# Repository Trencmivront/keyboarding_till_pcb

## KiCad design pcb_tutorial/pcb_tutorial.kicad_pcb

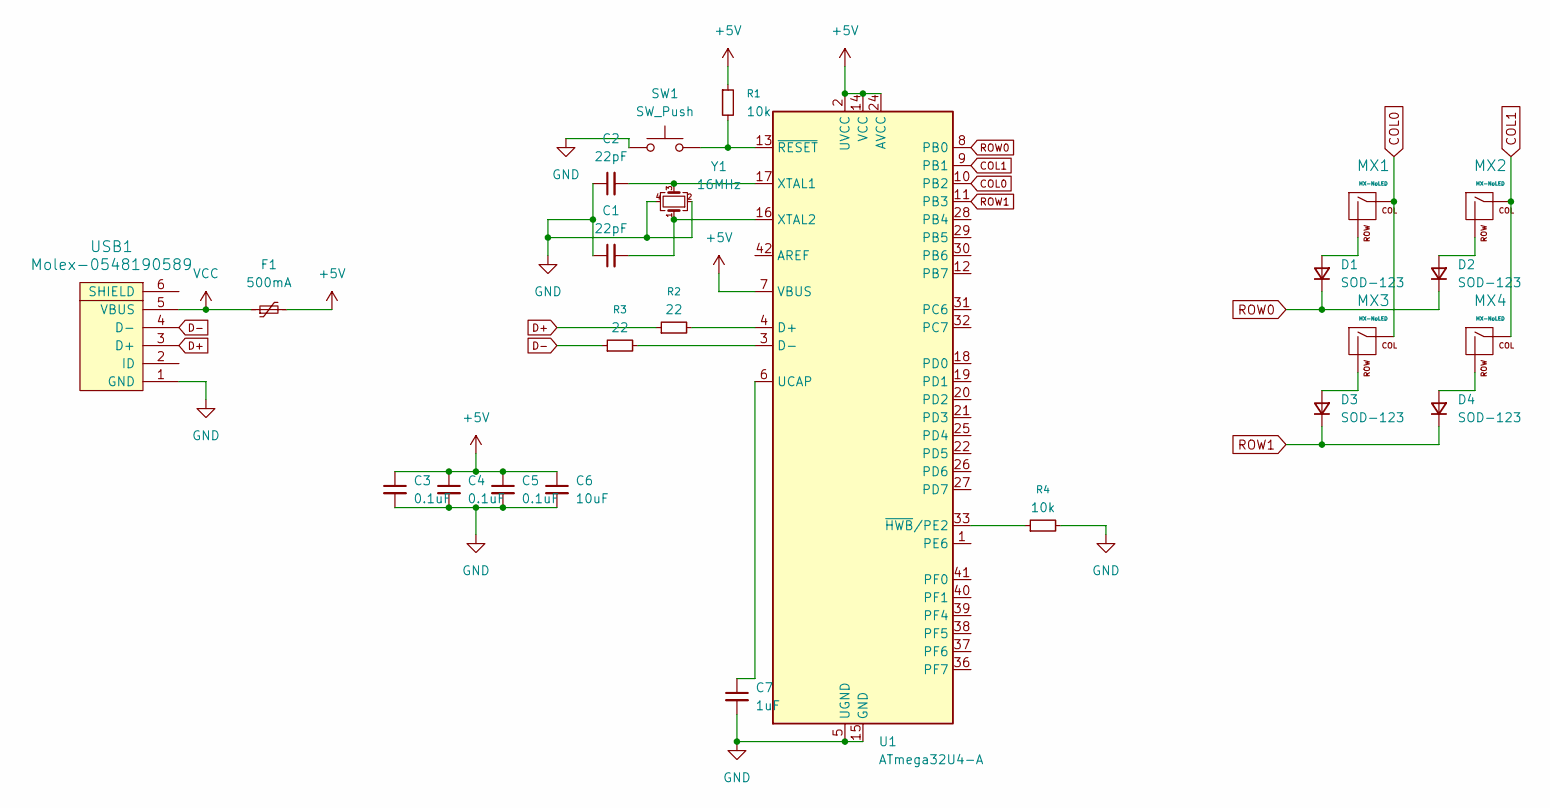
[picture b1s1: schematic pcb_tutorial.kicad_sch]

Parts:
C1, C2: 22pF; C_0805_2012Metric
C3, C4, C5: 0.1uF; C_0805_2012Metric
C6: 10uF; C_0805_2012Metric
C7: 1uF; C_0805_2012Metric
D1, D2, D3, D4: SOD-123; D_SOD-123
F1: 500mA; Fuse_1206_3216Metric
MX1, MX2, MX3, MX4: MX-NoLED; MX-1U-NoLED
R1, R4: 10k; R_0805_2012Metric
R2, R3: 22; R_0805_2012Metric
SW1: SW_Push; SKQG-1155865
U1: ATmega32U4-A; TQFP-44_10x10mm_P0.8mm
USB1: Molex-0548190589
Y1: 16MHz; Crystal_SMD_3225-4Pin_3.2x2.5mm

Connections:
+5V: C3.1, C4.1, C5.1, C6.1, F1.2, R1.1, U1.2 (UVCC), U1.7 (VBUS), U1.14 (VCC), U1.24 (AVCC), U1.34 (VCC), U1.44 (AVCC)
COL0: MX1.1 (COL), MX3.1 (COL), U1.10 (PB2)
COL1: MX2.1 (COL), MX4.1 (COL), U1.9 (PB1)
D+: R2.1, USB1.3 (D+)
D-: R3.1, USB1.4 (D-)
GND: C1.1, C2.1, C3.2, C4.2, C5.2, C6.2, C7.2, R4.2, SW1.1, U1.5 (UGND), U1.15 (GND), U1.23 (GND), U1.35 (GND), U1.43 (GND), USB1.1 (GND), Y1.2, Y1.4
unnamed: D1.2 (A), MX1.2 (ROW)
unnamed: D2.2 (A), MX2.2 (ROW)
unnamed: D3.2 (A), MX3.2 (ROW)
unnamed: D4.2 (A), MX4.2 (ROW)
unnamed: R2.2, U1.4 (D+)
unnamed: R3.2, U1.3 (D-)
unnamed: C7.1, U1.6 (UCAP)
unnamed: C2.2, U1.17 (XTAL1), Y1.3
unnamed: C1.2, U1.16 (XTAL2), Y1.1
unnamed: R4.1, U1.33 (~HWB/PE2)
unnamed: R1.2, SW1.2, U1.13 (~RESET)
ROW0: D1.1 (K), D2.1 (K), U1.8 (PB0)
ROW1: D3.1 (K), D4.1 (K), U1.11 (PB3)
VCC: F1.1, USB1.5 (VBUS)

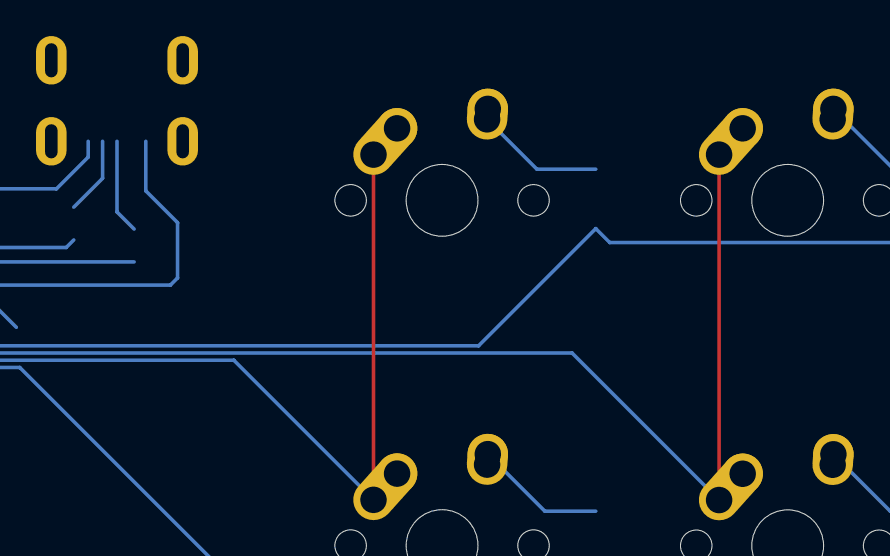
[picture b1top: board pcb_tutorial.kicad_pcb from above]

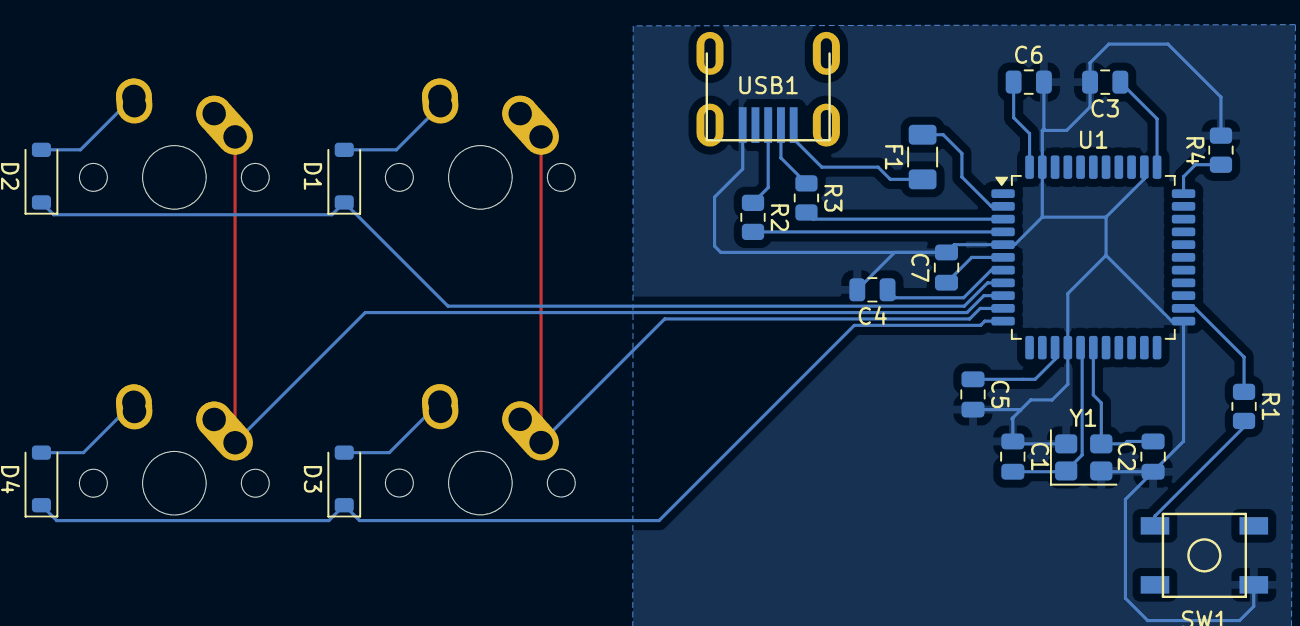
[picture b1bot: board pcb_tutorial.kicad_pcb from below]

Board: 2 copper layers, 24 parts (20 on the bottom side), 20 nets.

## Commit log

2025-10-13 Starting project
2025-10-14 submodules added
2025-10-14 Submodules
    Added submodules into the project file and integrated into project
2025-10-14 Adding components
    Adding some of the components
2025-10-15 moving on
2025-10-15 usb connector
2025-10-15 getting ready everything
2025-10-16 broke
2025-10-16 redoing the pcb part
2025-10-16 asdasd
2025-10-16 pcb components placed in their places
2025-10-18 Connecting components
    Making the worst designed pcb ever
2025-10-18 adding more lines
2025-10-18 Done
    The PCB is completed. And it looks really ugly.
2025-10-23 done?
